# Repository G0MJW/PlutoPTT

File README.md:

# PlutoPTT
PTT interface for Adlam-Pluto GPIO - Designed by F5OEO
Uses GPIO0 and GPIO1 - both to avoid unwanted PTT activation on Pluto boot.

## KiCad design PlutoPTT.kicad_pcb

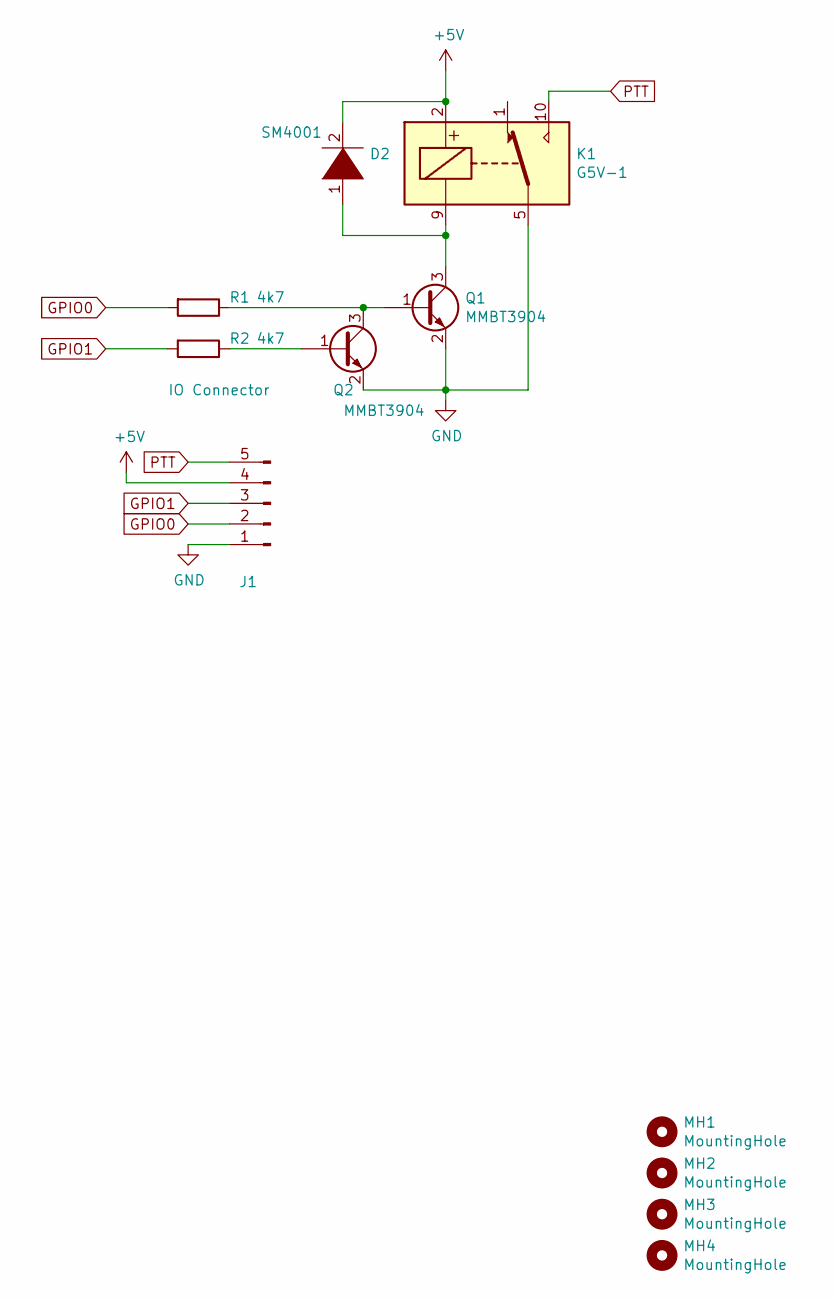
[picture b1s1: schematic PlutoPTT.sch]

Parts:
D2: SM4001; D_SMA_Handsoldering
J1: IO Connector; Molex_KK-254_AE-6410-05A_1x05_P2.54mm_Vertical
K1: G5V-1; Relay_SPDT_Omron_G5V-1
MH1, MH2, MH3, MH4: MountingHole; MountingHole_2.2mm_M2
Q1, Q2: MMBT3904; SOT-23
R1, R2: 4k7; R_0805_2012Metric_Pad1.15x1.40mm_HandSolder

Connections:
+5V: D2.2 (A), J1.4, K1.2
GND: J1.1, K1.5, K1.6, MH2.1, Q1.2 (E), Q2.2 (E)
GPIO0: J1.2, R1.2
GPIO1: J1.3, R2.2
unnamed: D2.1 (K), K1.9, Q1.3 (C)
unnamed: Q1.1 (B), Q2.3 (C), R1.1
unnamed: Q2.1 (B), R2.1
PTT: J1.5, K1.10

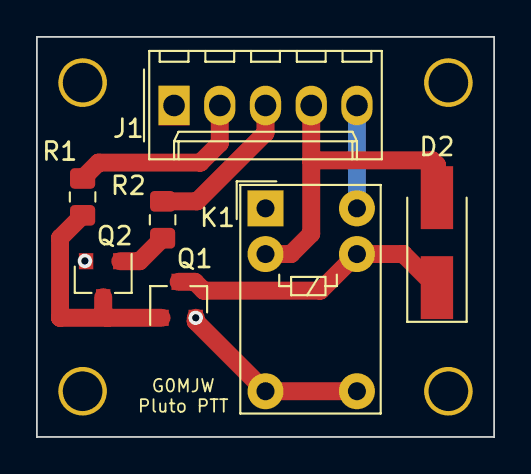
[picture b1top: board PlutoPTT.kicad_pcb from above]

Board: 2 copper layers, 25.4 x 22.2 mm, 11 parts (0 on the bottom side), 8 nets.
